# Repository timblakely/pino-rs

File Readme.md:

# Pino controller

Bare-metal BLDC controller for Pino the robot, written in
[Rust](https://www.rust-lang.org)!

-----

_**Disclaimer: I'm quite new at Rust, so please bear with me**_

This repository is currently a continuously changing, seething mess as I flail
around learning Rust. You're welcome to browse around the code, but please don't
expect proper, idiomatic Rust code just yet. For that I'd suggest the following
resources:

- [The Rust Book](https://doc.rust-lang.org/book/) - Seriously, read it "cover to cover" as it were. Coming from >15 years of C++ I debated whether it was worth reading the absolute basics, but I ended up going through it all and don't regret it one bit.
- [Embedded Rust Book](https://docs.rust-embedded.org/book/start/registers.html) - I know, I know, another book. But it's quite a bit shorter and more of a getting-started guide to getting Rust up and running in an embedded context.
- [m4vga-rs](https://github.com/cbiffle/m4vga-rs) - Not only is it a downright amazing implementation - 800x600@60FPS VGA on an STM32F4 (!) - the code is entirely in Rust and spectacularly well commented to boot! Definitely the place where I'm learning the most about Rust.

---

## Why rust?

I originally started the controller in C++, but found myself spending more and more time thinking about the language implementation, template metaprogramming, and wrestling with the inability to `constexpr` a raw address (can't `reinterpret_cast<Foo>` an address in a `constexpr`, but [don't take my word for it](https://www.youtube.com/watch?v=uwzuAGtAEFk&t=1217s)...), and less time on the actual controller itself. That's when I stumbled on Cliff Biffle's post with the contentious title "[Prefer Rust to C/++ for new code](http://cliffle.com/blog/prefer-rust/)". He posits that Rust was ready to replace C++ in most-if-not-all situations, _and that was back in 2019_. That post single-handedly convinced me to try out Rust, and I haven't looked back since.

## Building it

Don't bother trying right now; it doesn't really do anything :stuck_out_tongue_winking_eye:

But if you _really_ want to:

1. ```cargo build```
2. Connect your [NUCLEO-G474RE](https://www.st.com/en/evaluation-tools/nucleo-g474re.html), and follow the [Embedded Rust steps for adding the proper udev rules](https://docs.rust-embedded.org/book/intro/install/linux.html#udev-rules)
3. In VSCode, select `cortex-debug` launch configuraiton
4. Hit `F5`

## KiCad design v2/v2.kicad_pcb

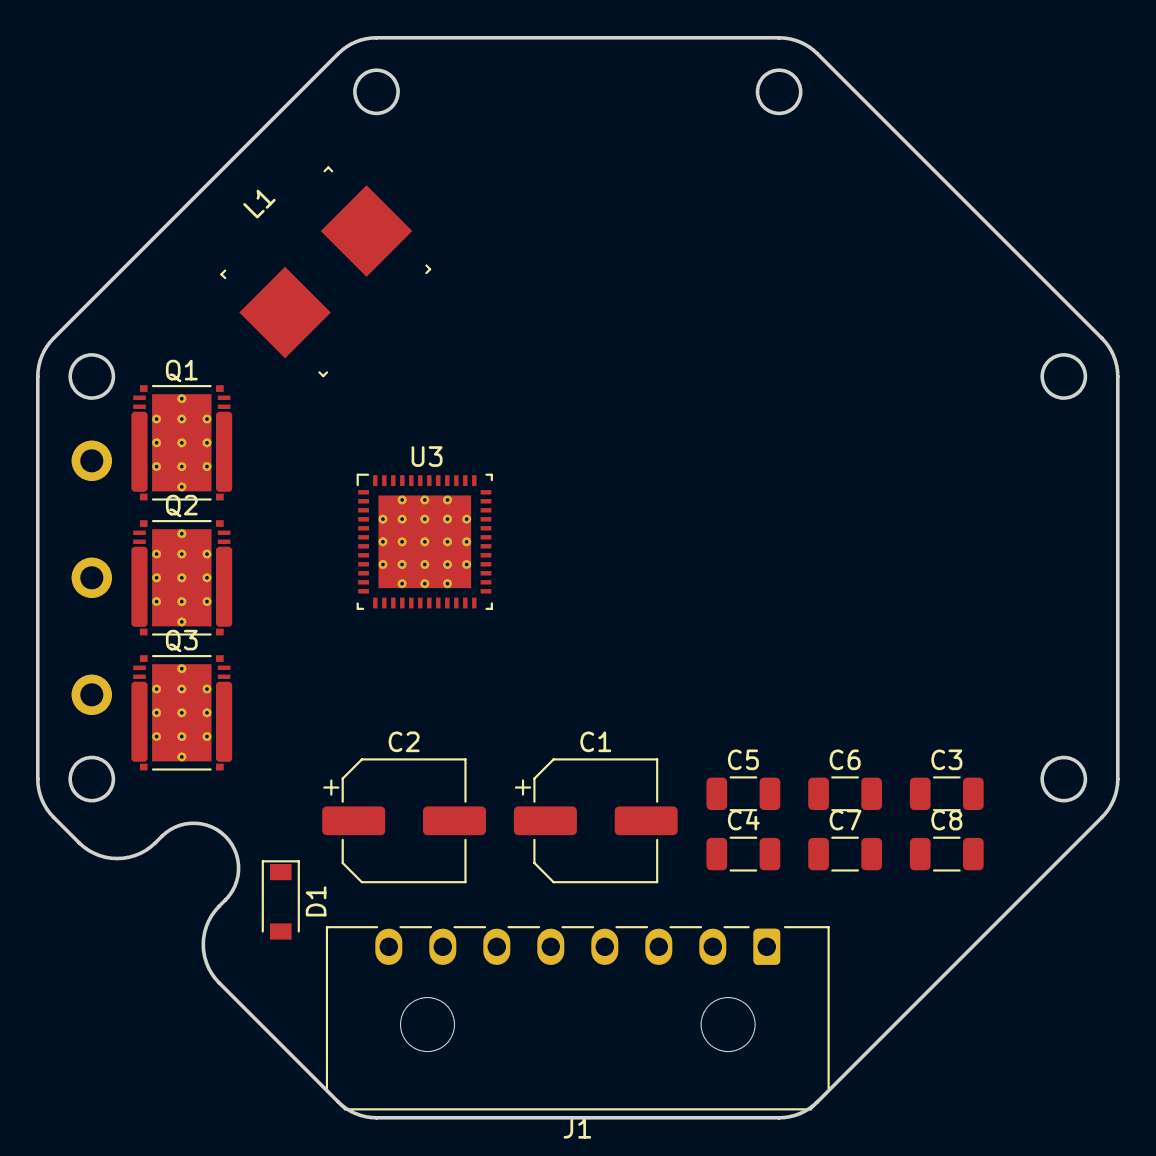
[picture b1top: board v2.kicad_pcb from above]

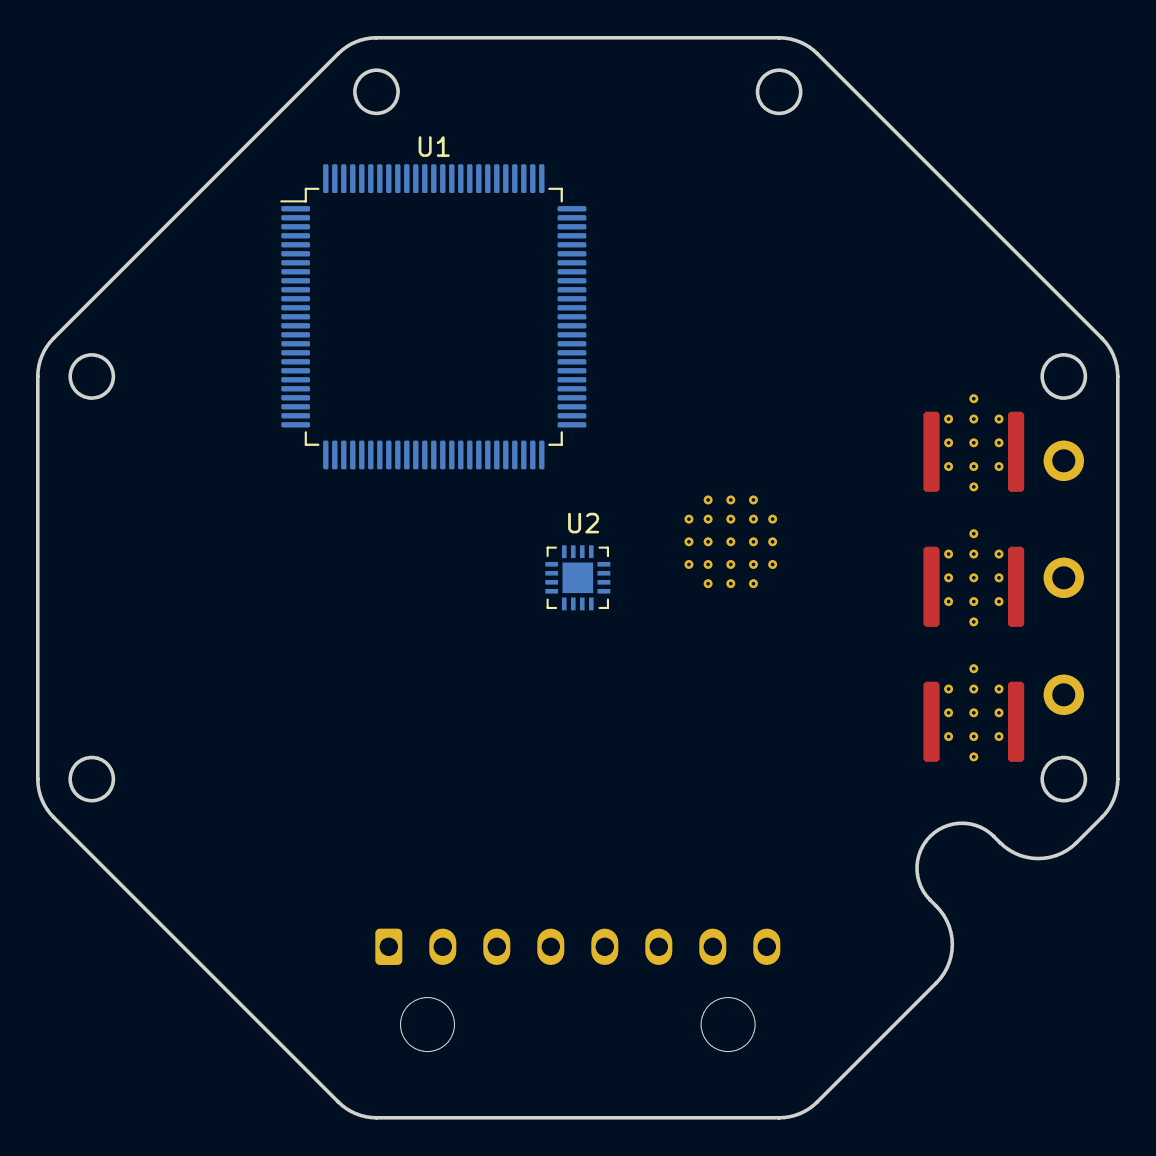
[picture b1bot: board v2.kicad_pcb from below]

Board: 4 copper layers, 60.0 x 60.0 mm, 20 parts (2 on the bottom side), 5 nets, no tracks yet.

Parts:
C1, C2: 22uF; CP_Elec_6.3x5.4
C3, C4, C5, C6, C7, C8: 10 uF; C_1206_3216Metric
D1: D_TVS; D_SOD-123
J1: Conn_01x08; Molex_Micro-Fit_3.0_43650-0800_1x08_P3.00mm_Horizontal
J2, J3, J4: PTH; PTH_1.28mm_ID_2.25mm_OD
L1: L; PCC-M0754M
Q1, Q2, Q3: CSD88599Q5DC; DMM0022A
U1: STM32H725VGT6; LQFP-100_14x14mm_P0.5mm
U2: MA702GQ-Z
U3: DRV8323RS; DRV8323RHRGZR

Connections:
unnamed: J2.1 (PTH), Q1.3 (VSW), Q1.4 (VSW), Q1.5 (VSW), Q1.6 (VSW), Q1.7 (VSW), Q1.8 (VSW), Q1.9 (VSW), Q1.10 (VSW), Q1.11 (VSW)
unnamed: J3.1 (PTH), Q2.3 (VSW), Q2.4 (VSW), Q2.5 (VSW), Q2.6 (VSW), Q2.7 (VSW), Q2.8 (VSW), Q2.9 (VSW), Q2.10 (VSW), Q2.11 (VSW)
unnamed: J4.1 (PTH), Q3.3 (VSW), Q3.4 (VSW), Q3.5 (VSW), Q3.6 (VSW), Q3.7 (VSW), Q3.8 (VSW), Q3.9 (VSW), Q3.10 (VSW), Q3.11 (VSW)
unnamed: U3.2 (PGND), U3.49 (PGND)
PGND: Q1.12 (PGND), Q1.13 (PGND), Q1.14 (PGND), Q1.15 (PGND), Q1.16 (PGND), Q1.17 (PGND), Q1.18 (PGND), Q1.19 (PGND), Q1.20 (PGND), Q2.12 (PGND), Q2.13 (PGND), Q2.14 (PGND), Q2.15 (PGND), Q2.16 (PGND), Q2.17 (PGND), Q2.18 (PGND), Q2.19 (PGND), Q2.20 (PGND), Q3.12 (PGND), Q3.13 (PGND), Q3.14 (PGND), Q3.15 (PGND), Q3.16 (PGND), Q3.17 (PGND), Q3.18 (PGND), Q3.19 (PGND), Q3.20 (PGND)

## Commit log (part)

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2021-03-26 Removed semihosting, added examples of graphing in cortex-debug
2021-03-26 Reorganized Readme a bit
2021-03-27 Clean up comments in openocd.gdb
2021-03-27 Work on clock startup
2021-03-28 Clock init
2021-03-28 Changed from generic 'app' name to 'bldc'
2021-03-29 Mostly notes on how stm32-rs does memory mapping. Also first stab at partial implementation of fdcan
2021-03-29 Baby steps towards fdcan memory map
2021-03-29 Read and write proxy working
2021-03-29 Broke out into proper locations
2021-03-30 Tested to make sure FDCAM SRAM writes worked
2021-03-30 Now zeroing FDCAN memory
2021-03-30 Trying out macros for field definitions
2021-03-30 Moved macros into bitfield
2021-03-30 Cleanup of bitfields and added rx_fifo
2021-03-31 Added extended_filter
2021-03-31 Made rx_fifo write only
2021-03-31 Tx fifo + mask fixes
2021-03-31 Static assertion on size of SramBlock
2021-04-01 Split ID fields into SID and EID
2021-04-01 Remove unused num-traits
2021-04-01 Moved code to Fdcan struct
2021-04-01 Cleanup
2021-04-01 Uncomment panic-halt since it's feature gated
2021-04-02 GPIO configuration working.
2021-04-03 Starting up FDCAN, but reference issues are messy still
2021-04-03 Solved compilation of fdcan
2021-04-03 Added some m4vga-rs code to third_party
2021-04-03 Cleaning up FDCAN init chain. Rust is really neato.
2021-04-04 FDCAN frame transmitted
2021-04-06 FDCAN works for transmission (no error checking yet)
2021-04-09 Add FDCAN Rx capability
2021-04-10 No need to copy another instance of FDCAN_RECEIVE_BUF
2021-04-10 Simplify static init for FDCAN
2021-04-10 Chain build and `cargo size` commands
2021-04-11 And presto, 1kHz SPI streaming!
2021-04-13 Broke out MA702 into its own implementation
2021-04-13 Initial work on DRV async registers
2021-04-13 Still need to configure GPIO pins, but so far so good
2021-04-14 DRV blocking startup
2021-04-16 All registers for DRV8323 set up (may have bugs)
2021-04-17 Configuring the DRV chip like Ben did
2021-04-17 Compiles, but sub-optimal
2021-04-18 Pausing DRV refactor for now; look into split borrowing for GPIO
2021-06-06 Working out latency between interrupt firing and entering interrupt handler
2021-06-12 Starting some notes on control theory
2021-06-14 Bootcamp ep 2
2021-06-14 Fix formatting of bootcamp 2
2021-06-19 Added notes from bootcamp part three
2021-06-23 Adding part 5 of control boot camp
2021-06-27 Control theory notes for part 6
2021-06-27 Fixing latex in Part 03
2021-06-27 CT Part 7
2021-06-28 Onwards to part 8!
2021-06-29 Part ten
2021-06-29 Minor correction to Part 10 eqn
2021-06-30 Through part 11
2021-06-30 First steps towards pendulum controller (part 12)
2021-07-02 Part 13
2021-07-26 Reorganizing notes; adding G4 docs
2021-07-26 Whitespace
2021-07-26 Cleanup of tasks.json
2021-07-26 Typo in main
2021-07-26 Prep for cargo fix
2021-07-29 Work on Park/Clark transforms
2021-07-29 Clarify which SPI port
2021-07-29 Add picture of BLDC V1.0
2021-07-29 Today's notes
2021-07-29 Fix weird markdown behavior
2021-07-29 Initial stab at systick sleep
2021-07-30 Notes checkin
2021-07-30 ADC4 calibration and startup
2021-07-30 Notes updates
2021-07-30 VBat sensing working pretty well, about 1% error.
2021-07-30 Reading Vrefint on ADC5
2021-07-31 Ad drv8323r datasheet
2021-07-31 Begin support for current sense ADCs
2021-08-02 Bold ;)
2021-08-02 Got the current sense triggering via hardware!
2021-08-02 Add quick note about interrupt handlers
2021-08-03 Got CORDIC working
2021-08-03 Fix notes
2021-08-03 Well, got the FETs to switch... and scream?
2021-08-04 PWMing the FETs!
2021-08-05 Fix Systick
2021-08-05 Fix DRV startup
2021-08-05 Phase A current sensing complete.
2021-08-07 Prior to reworking message structure
2021-08-07 Not liking the current approach
2021-08-07 New stab at FDCAN
2021-08-08 First real FDCAN message handling
2021-08-11 Getting info from FDCAN into the control loop
2021-08-11 First stab at BufferedState
2021-08-11 Starting commutation
2021-08-11 Not pretty, but it trampoline into callback works.
2021-08-11 Enabled Fn traits on IRef
2021-08-12 Comms and control loop up
2021-08-12 Passing hardware through to interrupt handler.
2021-08-15 Mainly notes over lapacians. Also modifying PWM on the fly
2021-08-15 Notes on control systems lectures
2021-08-17 More notes on calibration
2021-08-19 Moved SysTick into global blocking handler
2021-08-19 Converted DRV to use blocking_sleep
2021-08-19 Move drv calib into Drv8323rs
2021-08-20 Committing notes
2021-08-21 Square wave commutation works as expected
2021-08-21 Beginning inductance measurement calibration
2021-08-22 Current sensing in sane units
2021-08-22 Vuvuzelas and power supplies *sigh*
2021-08-24 Added a quick devnote
2021-08-25 Bootcamp notes
2021-08-25 Part 20
2021-08-25 Removed unncessary example code
2021-08-25 CTBC part 21
2021-08-25 Added note on RF connectors for scope grounding
2021-08-25 Reorganizing ee component notes
2021-08-25 CTBC Part 22
2021-08-27 More CTBC
2021-08-27 Added note on H7
2021-08-27 Messing around with Rigol in a notebook
2021-08-27 Disabling square wave generation while I'm working on sensing
2021-08-27 Characterizing ADC noise
2021-08-28 Part 25 of CTBC
2021-08-28 But why is the noise gone?!
2021-08-28 Part 25 committed
2021-08-29 Parts 26-29
2021-08-29 Quick 29
2021-08-29 Part 31
2021-08-29 Missed a parenthesis
2021-08-29 Corrected equation in Pt 31
2021-08-29 Quick note on a potential approach for commutation API
2021-08-29 Part 32
2021-08-31 34 and 35
2021-08-31 Added final screenshot to part 35
2021-08-31 Part 38
2021-08-31 Quick 38
2021-08-31 Some quick notes on Trait Objects in Rust
2021-09-03 First steps towards using heap
2021-09-03 First stab at dynamic commutation loops
2021-09-07 FDCAN suddenly not working?
2021-09-07 Current sensing triggered via FDCAN
2021-09-08 Update gitignore
2021-09-08 Pretty ugly, but FDCAN current sense working
2021-09-08 CallbackCurrentSensor is a bit more ergonomic
2021-09-08 Move box declarations into commutator
2021-09-08 Centralizing heap initialization
2021-09-08 Remove testing IdleCurrentSensor.
2021-09-08 Move ADC handler into commutation
2021-09-08 Exposed hardware to control loop
2021-09-09 Enabled current sense calibration during run
2021-09-09 IdleCurrentHistogram
2021-09-10 Various notes
2021-09-10 Split commutation up into separate files
2021-09-10 Beginning inductance mods
2021-09-11 Fix math typo
2021-09-11 Close to measurement
2021-09-11 Add note for rev1.1
2021-09-11 Inductances!
2021-09-12 Increaes ADC calibration during startup to 2s
2021-09-12 Devnotes
2021-09-13 Adding more variables to inductance measurements
2021-09-14 Quick comment update in current_sensing
2021-09-14 Rename inductance_measurement
2021-09-14 Add some safety measures on commutation completion
2021-09-15 Current measurement success
2021-09-17 Control loop notes
2021-09-18 Change resistance calib to be relative to Vbus
2021-09-19 Current-controlled loop. No more blowing up stators!
2021-09-22 Added note for v1.1 vias
2021-09-22 Devlog
2021-09-22 Backlog of notes
2021-09-23 Initial work on encoder: enabling DMA1 interrupt.
2021-09-23 Set correct priorities for the four interrupts
2021-09-23 Bare encoder reading works
2021-09-24 Removed unsafe from buffered_state
2021-09-24 Calculating angle physics at 1kHz
2021-09-24 Removed unnecessary lifetimes from BufferedState
2021-09-24 Angle sensing up and running
    Moved tim3 into the MA702 and corrected the angle calculation.
2021-09-24 Swap out MA702 for higher level encoder.
2021-09-24 Combine both locks in MA702 DMA interrupt.
2021-09-24 Enable G and R LED GPIOs.
2021-09-24 Correct DMA settings for MA702
2021-09-24 Move tim3 configuration into MA702
2021-09-24 Pump MA702 polling to 100kHz
2021-09-24 Dev notes
2021-09-24 Add polling version of MA702
2021-09-24 Encoder and ma702 calculating electrical angle
    Includes rollover compensation and total angle calculation
2021-09-25 Move PI controller into its own file
2021-09-25 Add pole pairs to MA702
2021-09-26 First stab at CORDIC
2021-09-26 Quick fix for Cordic linearization
2021-09-27 Initial FOC steps
2021-09-27 Getting at least a bit of commutation but something's broken
2021-09-27 Added ability to read encoder remotely via FDCAN
2021-09-27 A few struct renames and inverting PWM signals in FoC
2021-09-28 Add badly hacked LED control
2021-09-28 Prevent windup in PI controller
2021-09-28 Allow LED's `on_while` to return a value
2021-09-28 Add LED Pulsing to calibrate_e_zero
2021-09-28 Separate ExtendedFdcanFrame into outgoing/incoming
2021-09-29 Dead code removal from main
2021-09-29 Messing around trying to get FDCAN to do dynamic handling
2021-09-29 FDCAN dynamic dispatch
    Doing some shady things with lifetimes, but seems to work for now.
2021-10-03 Major refactor of FDCAN part 1
    * Cleanup of the FDCAN messages into their respective files
    * Introduced a `Message` enum to avoid ID stomping
2021-10-03 More steps towards cleaning up FDCAN
    * Peripheral and SRAM no longer public
    * Removed uninit stage.
2021-10-03 Simplify FDCAN more
    - Have callbacks own FdcanMessage
    - Don't block interrupts when handling received messages
2021-10-03 Correct ControlLoop trait
2021-10-03 Note on new single-package BLDC
2021-10-03 Centralize commutation.
2021-10-04 First steps towards moving to PWM struct
2021-10-04 Extricated timer functionality into PWM
2021-10-04 Remove edition2021 now that it's stable
2021-10-04 Renamed TorqueControl and moved to FoC
2021-10-05 Lower update rate of MA702 to 50kHz to save some cycles
2021-10-06 Still working on getting velocity control
2021-10-06 Old notes
2021-10-06 Where'd that file come from?
2021-10-06 Rename root cargo config
2021-10-06 Reorganize the cargo layout
2021-10-07 Modify settings to allow rust-analyzer to work again
2021-10-07 Dummy reply message for CalibrateEZero
2021-10-07 Rename documents
2021-10-08 Rename launch targets
2021-10-09 Refactor messages out for fdcom
2021-10-09 Swap magic number for actual peripheral in LED
2021-10-09 Added explicit on/off for LEDs
2021-10-09 Remove redundant Sized attribute in BufferedState
2021-10-09 Added spin command to fdcom
2021-10-09 Centralized sensor state
2021-10-10 Update SensorState to use SeqLock
2021-10-10 Host tests up and running, but quite ugly feature configs
2021-10-11 More fixes for host compilation. Still have an odd warning
2021-10-11 Enable doctests for bldc again
2021-10-11 Unit tests and bugfix for iteratively_calculate_timer_config
2021-10-11 Added schedule-able callback on TIM2
2021-10-11 Enable variable freq state streaming via FDCAN
2021-10-12 Remove one instance of transmute
2021-10-12 Separate host tooling/tests since Cargo doesn't play nice with them
2021-10-12 Remove warning from std-compatible float messages
2021-10-16 Note on easing functions
2021-10-16 Rudimentary Pos/Vel observer
2021-10-17 Add PLLObserver from radians
2021-10-17 Note on un-briking an un-flashable g4
2021-10-17 Clean up initial state of Encoder
2021-10-17 Centralized encoder state into encoder
2021-11-21 Notes on board
2021-11-21 Change encoder bandwidth to 200 rads/s
2021-11-21 Notes on isolators
2021-11-21 Removed one box
2021-11-21 Removed another box
2021-11-22 Ugly fdcan message handling
2021-11-22 Slightly better pattern
2021-11-22 Message enum working.
2021-11-22 Updated control loop to use enum_dispatch
2021-11-22 Removed all references to dynamic allocation
2021-11-22 Removed all custom allocation
2021-11-22 Pull out commutator into own lib
2021-11-22 Remove iref to allow for stable compilation
2021-11-23 Add note on why we're using our own enum_dispatch
2021-11-23 Initial support for dynamic dispatch
2021-11-23 Macro-ized MessageHandler
2021-11-23 Added IDs and enabled torque control
2021-11-23 Consolidated Intos
2021-11-24 Simplify API for message handling
2021-11-24 Add SetPosVel message handler
2021-11-24 Move PosVelState out
2021-11-24 Rename some fields to be more logical
2021-11-24 Finally zeroing in on naming schemes
2021-11-25 Refactor controller into its own struct; compiling again
2021-11-25 Reenabled fdcan commands
2021-11-26 Plumbing LoopState into control loops
2021-11-26 Added support for shutting down control loop.
2021-11-28 Migrating to pending upstream stm32g4 changes
2022-01-31 Add v2 KiCad project

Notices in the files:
parts and their libraries:
Copyright 2021 Accelerated Designs. All rights reserved.
